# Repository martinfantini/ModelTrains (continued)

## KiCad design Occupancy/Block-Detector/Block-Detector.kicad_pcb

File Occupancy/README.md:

# ModelTrains

This repository contains all the necesarry information to develop an model trains mock-up

## DCC Central

Here is all the information related to the DCC central, which has a DCC booster, to have more than 2A of the output current.

## Expander

Here is the expander connected to the central, to have more input/output configuation.

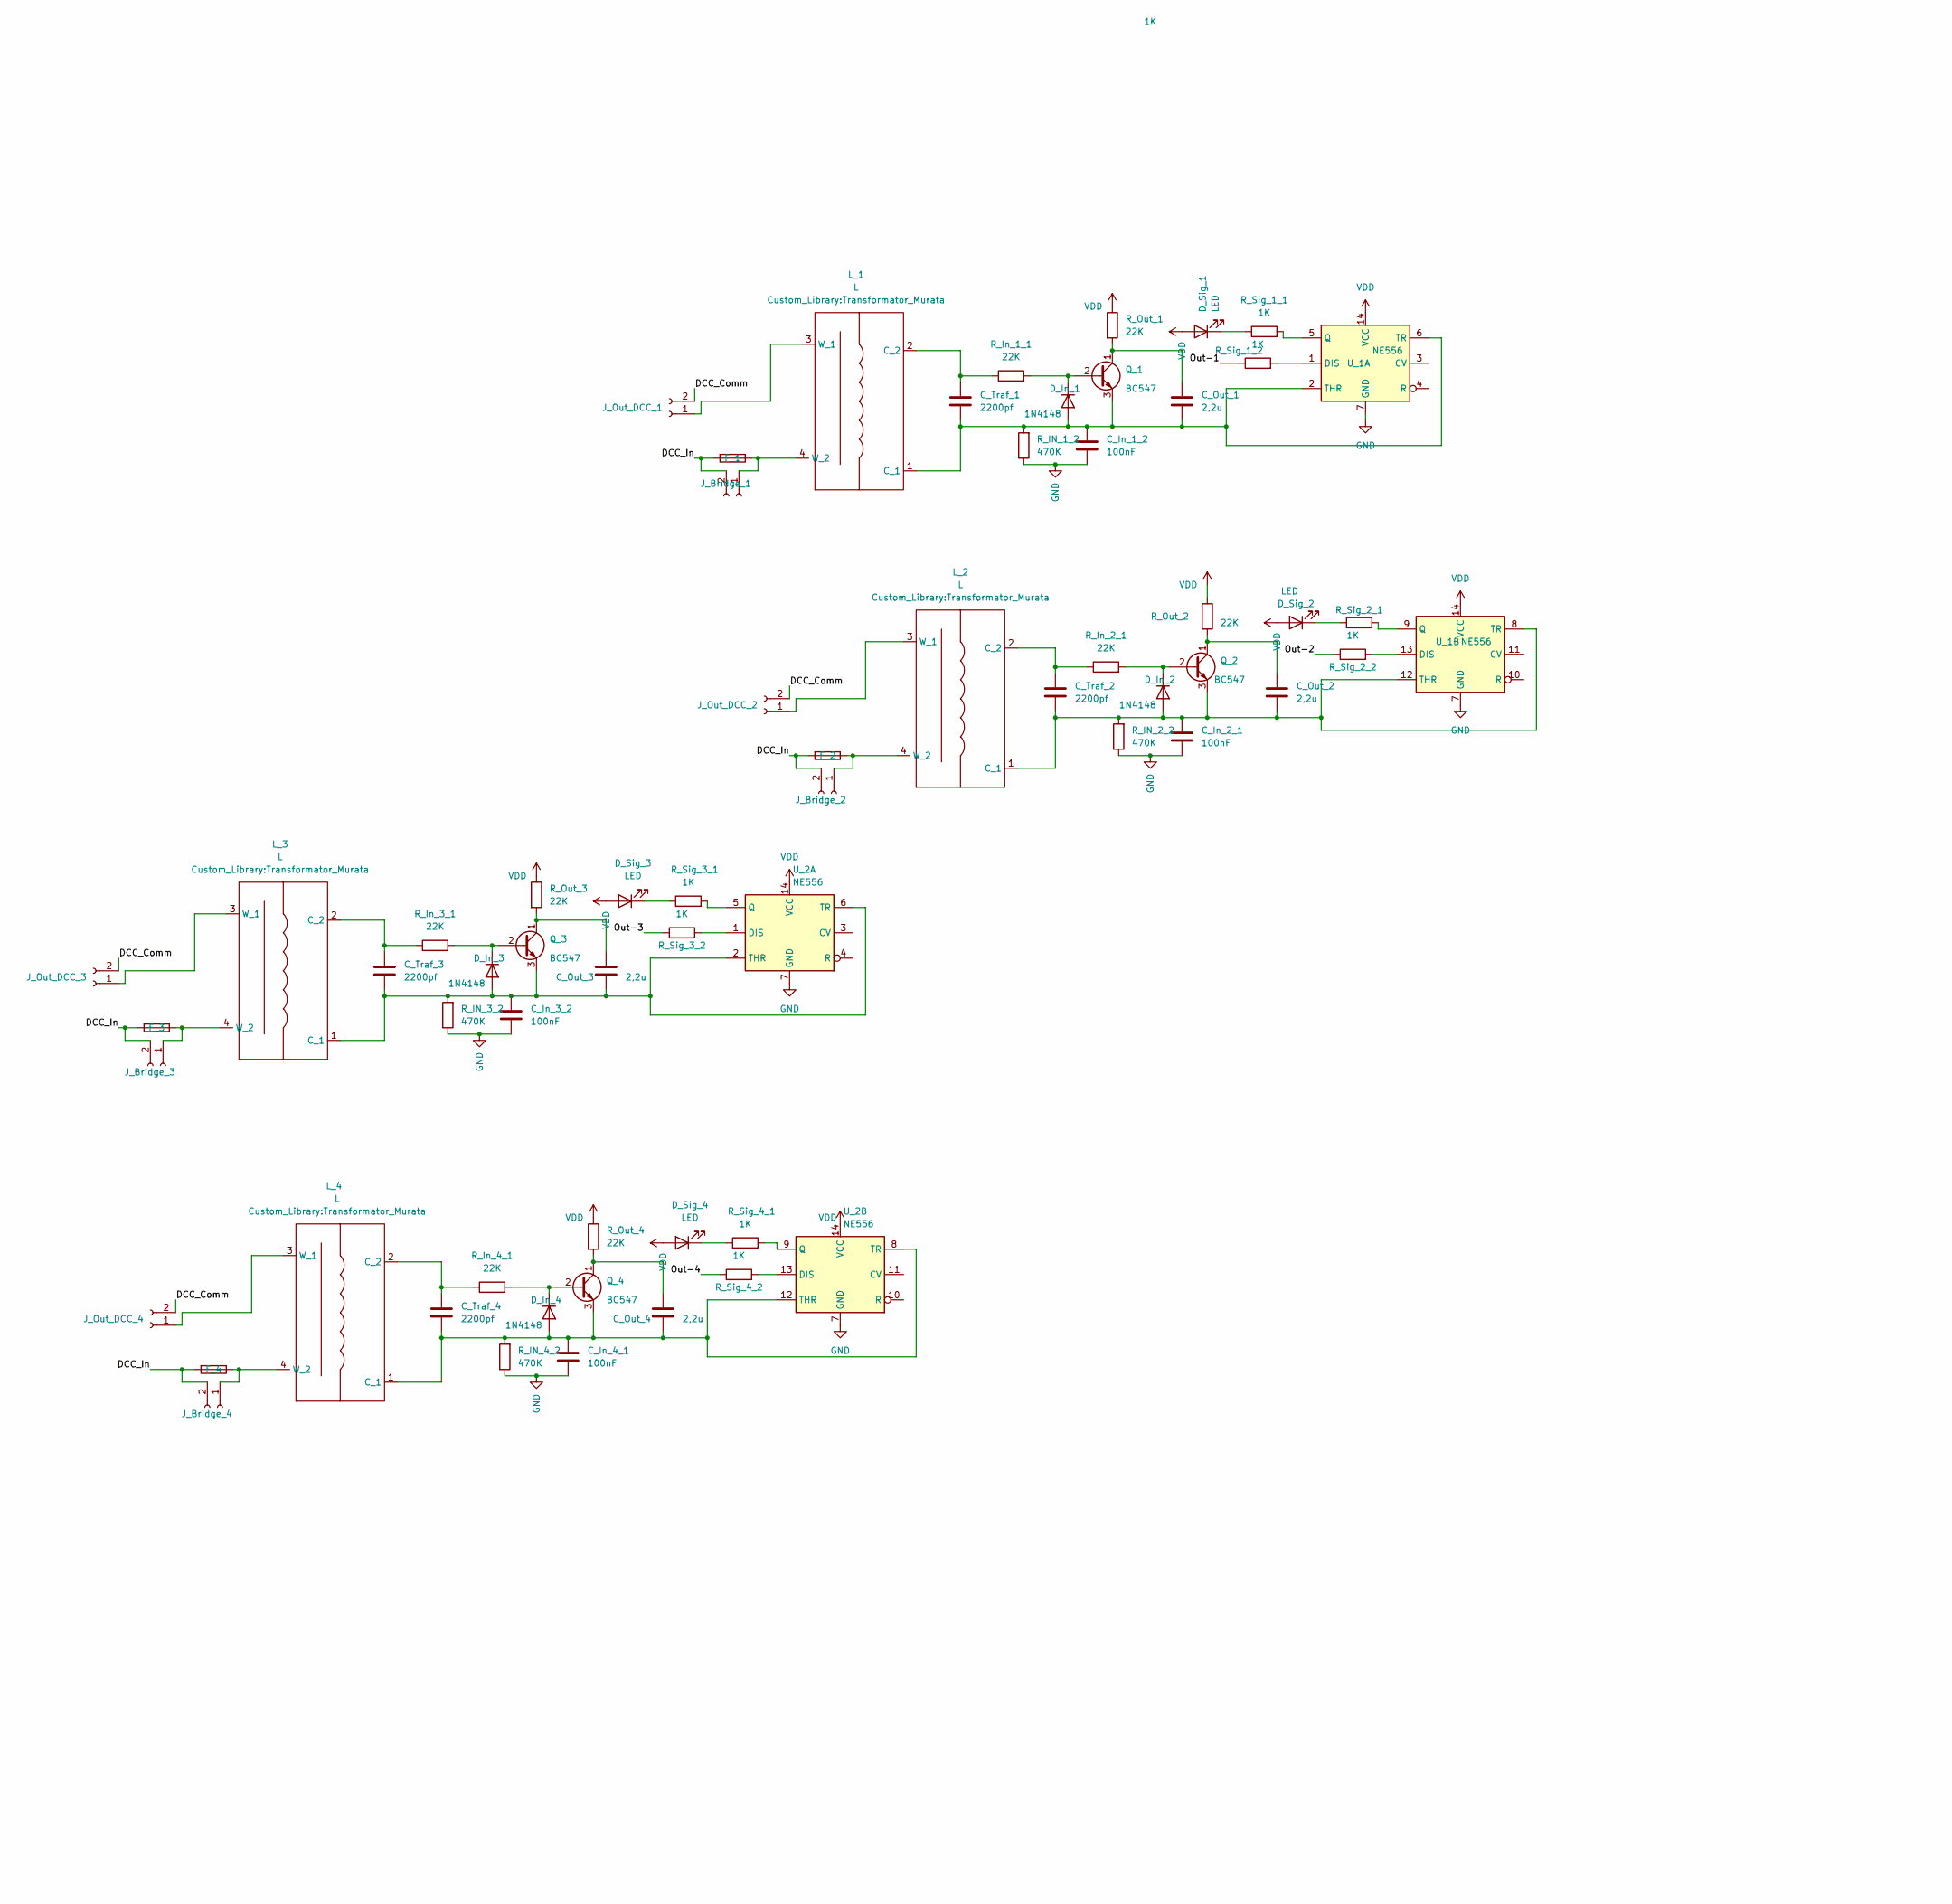
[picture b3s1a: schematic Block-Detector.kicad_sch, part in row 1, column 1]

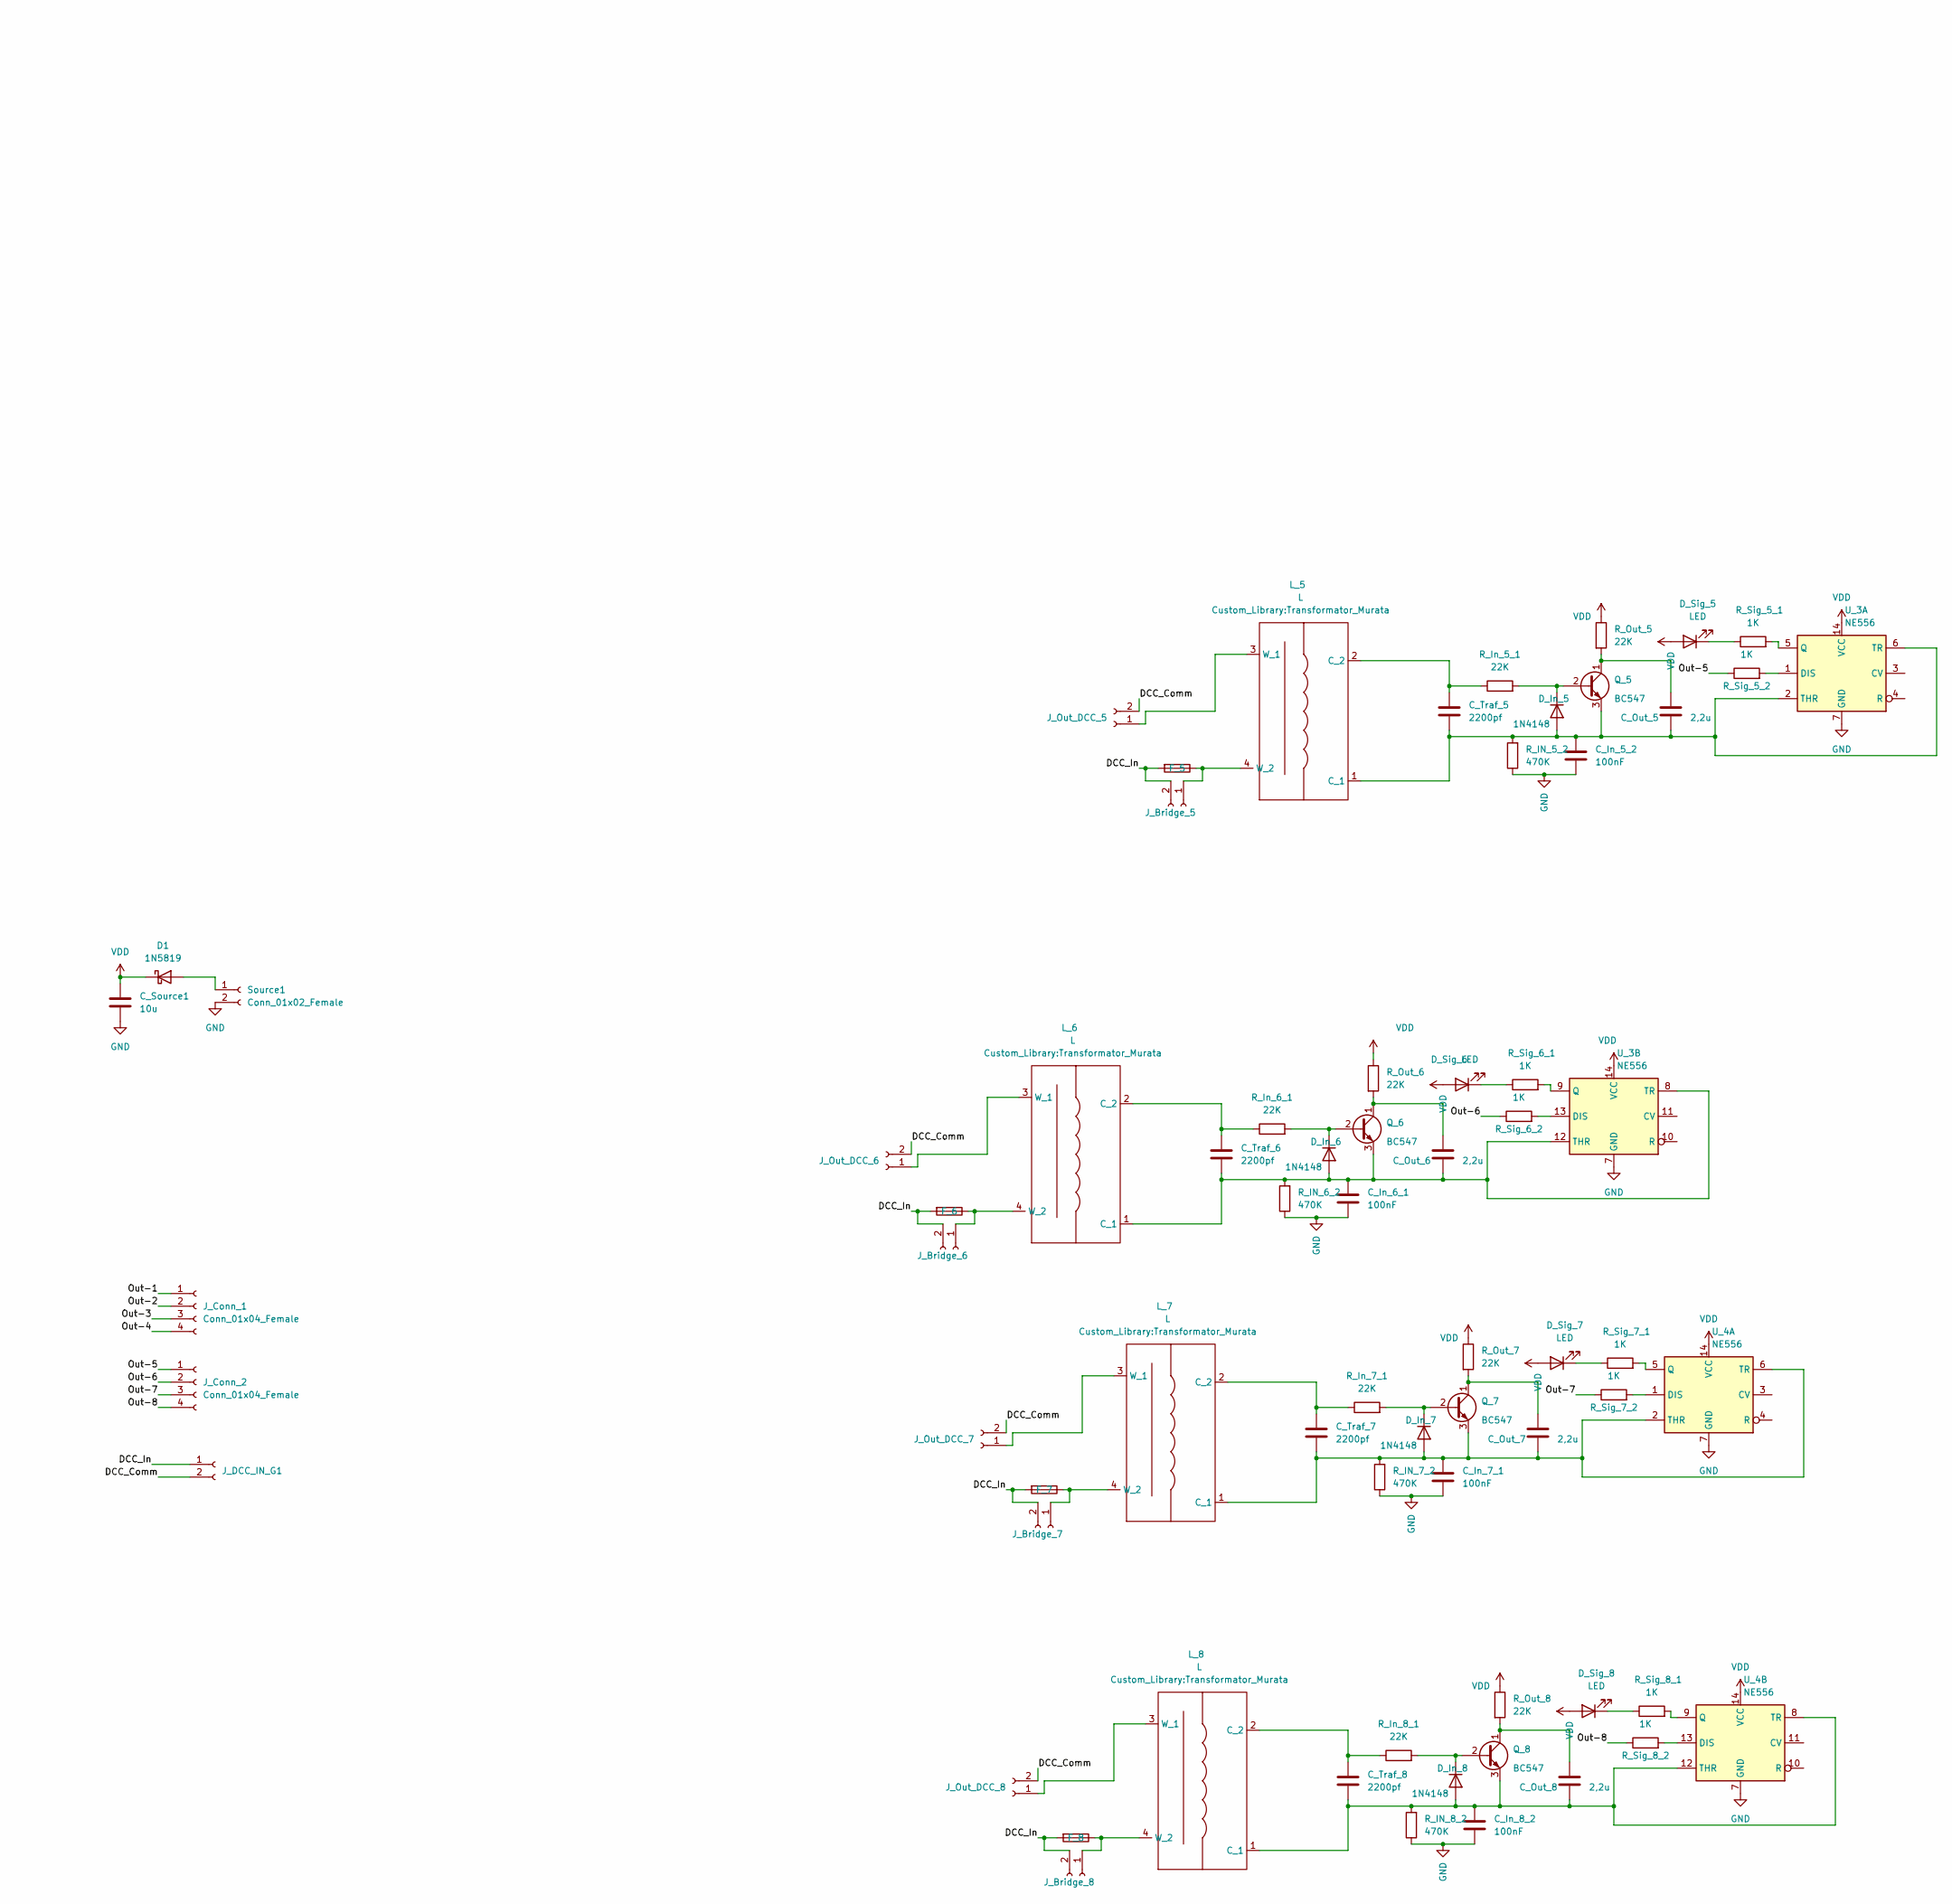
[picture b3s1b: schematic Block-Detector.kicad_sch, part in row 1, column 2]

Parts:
C_In_1_2, C_In_2_1, C_In_3_2, C_In_4_1, C_In_5_2, C_In_6_1, C_In_7_1, C_In_8_2: 100nF; C_Disc_D3.8mm_W2.6mm_P2.50mm
C_Out_1, C_Out_2, C_Out_3, C_Out_4, C_Out_5, C_Out_6, C_Out_7, C_Out_8: 2,2u; C_Disc_D3.8mm_W2.6mm_P2.50mm
C_Source1: 10u; C_Axial_L3.8mm_D2.6mm_P7.50mm_Horizontal
C_Traf_1, C_Traf_2, C_Traf_3, C_Traf_4, C_Traf_5, C_Traf_6, C_Traf_7, C_Traf_8: 2200pf; C_Rect_L7.0mm_W2.5mm_P5.00mm
D1: 1N5819; D_DO-41_SOD81_P10.16mm_Horizontal
D_In_1, D_In_2, D_In_3, D_In_4, D_In_5, D_In_6, D_In_7, D_In_8: 1N4148; D_DO-35_SOD27_P7.62mm_Horizontal
D_Sig_1, D_Sig_2, D_Sig_3, D_Sig_4, D_Sig_5, D_Sig_6, D_Sig_7, D_Sig_8: LED; LED_D5.0mm
F_1, F_2, F_3, F_4, F_5, F_6, F_7, F_8: 1A; Fuseholder_Clip-5x20mm_Keystone_3512_Inline_P23.62x7.27mm_D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
J_Bridge_1, J_Bridge_2, J_Bridge_3, J_Bridge_4, J_Bridge_5, J_Bridge_6, J_Bridge_7, J_Bridge_8: Conn_01x02_Female; LED_2512_6332Metric
J_Conn_1, J_Conn_2: Conn_01x04_Female; Wago_734-134_1x04_P3.50mm_Vertical
J_DCC_IN_G1: Conn_01x02_Female; Wago_734-132_1x02_P3.50mm_Vertical
J_Out_DCC_1, J_Out_DCC_2, J_Out_DCC_3, J_Out_DCC_4, J_Out_DCC_5, J_Out_DCC_6, J_Out_DCC_7, J_Out_DCC_8: Conn_01x02_Female; Wago_734-132_1x02_P3.50mm_Vertical
L_1, L_2, L_3, L_4, L_5, L_6, L_7, L_8: L; Transformator_Murata
Q_1, Q_2, Q_3, Q_4, Q_5, Q_6, Q_7, Q_8: BC547; TO-92_Inline
R_IN_1_2, R_IN_2_2, R_IN_3_2, R_IN_4_2, R_IN_5_2, R_IN_6_2, R_IN_7_2, R_IN_8_2: 470K; R_Axial_DIN0309_L9.0mm_D3.2mm_P12.70mm_Horizontal
R_In_1_1, R_In_2_1, R_In_3_1, R_In_4_1, R_In_5_1, R_In_6_1, R_In_7_1, R_In_8_1: 22K; R_Axial_DIN0309_L9.0mm_D3.2mm_P12.70mm_Horizontal
R_Out_1, R_Out_2, R_Out_3, R_Out_4, R_Out_5, R_Out_6, R_Out_7, R_Out_8: 22K; R_Axial_DIN0309_L9.0mm_D3.2mm_P12.70mm_Horizontal
R_Sig_1_1, R_Sig_1_2, R_Sig_2_1, R_Sig_2_2, R_Sig_3_1, R_Sig_3_2, R_Sig_4_1, R_Sig_4_2, R_Sig_5_1, R_Sig_5_2, R_Sig_6_1, R_Sig_6_2, R_Sig_7_1, R_Sig_7_2, R_Sig_8_1, R_Sig_8_2: 1K; R_Axial_DIN0309_L9.0mm_D3.2mm_P12.70mm_Horizontal
Source1: Conn_01x02_Female; JST_NV_B02P-NV_1x02_P5.00mm_Vertical
U_1, U_2, U_3, U_4: NE556; DIP-14_W7.62mm_Socket_LongPads

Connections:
/DCC_Comm: J_DCC_IN_G1.2, J_Out_DCC_1.2, J_Out_DCC_2.2, J_Out_DCC_3.2, J_Out_DCC_4.2, J_Out_DCC_5.2, J_Out_DCC_6.2, J_Out_DCC_7.2, J_Out_DCC_8.2
/DCC_In: F_1.2, F_2.2, F_3.2, F_4.2, F_5.2, F_6.2, F_7.2, F_8.2, J_Bridge_1.2, J_Bridge_2.2, J_Bridge_3.2, J_Bridge_4.2, J_Bridge_5.2, J_Bridge_6.2, J_Bridge_7.2, J_Bridge_8.2, J_DCC_IN_G1.1
/Out-1: J_Conn_1.1, R_Sig_1_2.1
/Out-2: J_Conn_1.2, R_Sig_2_2.1
/Out-3: J_Conn_1.3, R_Sig_3_2.1
/Out-4: J_Conn_1.4, R_Sig_4_2.1
/Out-5: J_Conn_2.1, R_Sig_5_2.1
/Out-6: J_Conn_2.2, R_Sig_6_2.1
/Out-7: J_Conn_2.3, R_Sig_7_2.1
/Out-8: J_Conn_2.4, R_Sig_8_2.1
GND: C_In_1_2.2, C_In_2_1.2, C_In_3_2.2, C_In_4_1.2, C_In_5_2.2, C_In_6_1.2, C_In_7_1.2, C_In_8_2.2, C_Source1.2, R_IN_1_2.1, R_IN_2_2.1, R_IN_3_2.1, R_IN_4_2.1, R_IN_5_2.1, R_IN_6_2.1, R_IN_7_2.1, R_IN_8_2.1, Source1.2, U_1.7 (GND), U_2.7 (GND), U_3.7 (GND), U_4.7 (GND)
unnamed: C_In_1_2.1, C_Out_1.2, C_Traf_1.2, D_In_1.2 (A), L_1.1 (C_1), Q_1.3 (E), R_IN_1_2.2, U_1.2 (THR), U_1.6 (TR)
unnamed: C_In_2_1.1, C_Out_2.2, C_Traf_2.2, D_In_2.2 (A), L_2.1 (C_1), Q_2.3 (E), R_IN_2_2.2, U_1.8 (TR), U_1.12 (THR)
unnamed: C_In_3_2.1, C_Out_3.2, C_Traf_3.2, D_In_3.2 (A), L_3.1 (C_1), Q_3.3 (E), R_IN_3_2.2, U_2.2 (THR), U_2.6 (TR)
unnamed: C_In_4_1.1, C_Out_4.2, C_Traf_4.2, D_In_4.2 (A), L_4.1 (C_1), Q_4.3 (E), R_IN_4_2.2, U_2.8 (TR), U_2.12 (THR)
unnamed: C_In_5_2.1, C_Out_5.2, C_Traf_5.2, D_In_5.2 (A), L_5.1 (C_1), Q_5.3 (E), R_IN_5_2.2, U_3.2 (THR), U_3.6 (TR)
unnamed: C_In_6_1.1, C_Out_6.2, C_Traf_6.2, D_In_6.2 (A), L_6.1 (C_1), Q_6.3 (E), R_IN_6_2.2, U_3.8 (TR), U_3.12 (THR)
unnamed: C_In_7_1.1, C_Out_7.2, C_Traf_7.2, D_In_7.2 (A), L_7.1 (C_1), Q_7.3 (E), R_IN_7_2.2, U_4.2 (THR), U_4.6 (TR)
unnamed: C_In_8_2.1, C_Out_8.2, C_Traf_8.2, D_In_8.2 (A), L_8.1 (C_1), Q_8.3 (E), R_IN_8_2.2, U_4.8 (TR), U_4.12 (THR)
unnamed: C_Out_1.1, Q_1.1 (C), R_Out_1.2
unnamed: C_Out_2.1, Q_2.1 (C), R_Out_2.2
unnamed: C_Out_3.1, Q_3.1 (C), R_Out_3.2
unnamed: C_Out_4.1, Q_4.1 (C), R_Out_4.2
unnamed: C_Out_5.1, Q_5.1 (C), R_Out_5.2
unnamed: C_Out_6.1, Q_6.1 (C), R_Out_6.2
unnamed: C_Out_7.1, Q_7.1 (C), R_Out_7.2
unnamed: C_Out_8.1, Q_8.1 (C), R_Out_8.2
unnamed: C_Traf_1.1, L_1.2 (C_2), R_In_1_1.1
unnamed: C_Traf_2.1, L_2.2 (C_2), R_In_2_1.1
unnamed: C_Traf_3.1, L_3.2 (C_2), R_In_3_1.1
unnamed: C_Traf_4.1, L_4.2 (C_2), R_In_4_1.1
unnamed: C_Traf_5.1, L_5.2 (C_2), R_In_5_1.1
unnamed: C_Traf_6.1, L_6.2 (C_2), R_In_6_1.1
unnamed: C_Traf_7.1, L_7.2 (C_2), R_In_7_1.1
unnamed: C_Traf_8.1, L_8.2 (C_2), R_In_8_1.1
unnamed: D1.2 (A), Source1.1
unnamed: D_In_1.1 (K), Q_1.2 (B), R_In_1_1.2
unnamed: D_In_2.1 (K), Q_2.2 (B), R_In_2_1.2
unnamed: D_In_3.1 (K), Q_3.2 (B), R_In_3_1.2
unnamed: D_In_4.1 (K), Q_4.2 (B), R_In_4_1.2
unnamed: D_In_5.1 (K), Q_5.2 (B), R_In_5_1.2
unnamed: D_In_6.1 (K), Q_6.2 (B), R_In_6_1.2
unnamed: D_In_7.1 (K), Q_7.2 (B), R_In_7_1.2
unnamed: D_In_8.1 (K), Q_8.2 (B), R_In_8_1.2
unnamed: D_Sig_1.1 (K), R_Sig_1_1.1
unnamed: D_Sig_2.1 (K), R_Sig_2_1.1
unnamed: D_Sig_3.1 (K), R_Sig_3_1.1
unnamed: D_Sig_4.1 (K), R_Sig_4_1.1
unnamed: D_Sig_5.1 (K), R_Sig_5_1.1
unnamed: D_Sig_6.1 (K), R_Sig_6_1.1
unnamed: D_Sig_7.1 (K), R_Sig_7_1.1
unnamed: D_Sig_8.1 (K), R_Sig_8_1.1
unnamed: F_1.1, J_Bridge_1.1, L_1.4 (W_2)
unnamed: F_2.1, J_Bridge_2.1, L_2.4 (W_2)
unnamed: F_3.1, J_Bridge_3.1, L_3.4 (W_2)
unnamed: F_4.1, J_Bridge_4.1, L_4.4 (W_2)
unnamed: F_5.1, J_Bridge_5.1, L_5.4 (W_2)
unnamed: F_6.1, J_Bridge_6.1, L_6.4 (W_2)
unnamed: F_7.1, J_Bridge_7.1, L_7.4 (W_2)
unnamed: F_8.1, J_Bridge_8.1, L_8.4 (W_2)
unnamed: J_Out_DCC_1.1, L_1.3 (W_1)
unnamed: J_Out_DCC_2.1, L_2.3 (W_1)
unnamed: J_Out_DCC_3.1, L_3.3 (W_1)
unnamed: J_Out_DCC_4.1, L_4.3 (W_1)
unnamed: J_Out_DCC_5.1, L_5.3 (W_1)
unnamed: J_Out_DCC_6.1, L_6.3 (W_1)
unnamed: J_Out_DCC_7.1, L_7.3 (W_1)
unnamed: J_Out_DCC_8.1, L_8.3 (W_1)
unnamed: R_Sig_1_1.2, U_1.5 (Q)
unnamed: R_Sig_1_2.2, U_1.1 (DIS)
unnamed: R_Sig_2_1.2, U_1.9 (Q)
unnamed: R_Sig_2_2.2, U_1.13 (DIS)
unnamed: R_Sig_3_1.2, U_2.5 (Q)
unnamed: R_Sig_3_2.2, U_2.1 (DIS)
unnamed: R_Sig_4_1.2, U_2.9 (Q)
unnamed: R_Sig_4_2.2, U_2.13 (DIS)
unnamed: R_Sig_5_1.2, U_3.5 (Q)
unnamed: R_Sig_5_2.2, U_3.1 (DIS)
unnamed: R_Sig_6_1.2, U_3.9 (Q)
unnamed: R_Sig_6_2.2, U_3.13 (DIS)
unnamed: R_Sig_7_1.2, U_4.5 (Q)
unnamed: R_Sig_7_2.2, U_4.1 (DIS)
unnamed: R_Sig_8_1.2, U_4.9 (Q)
unnamed: R_Sig_8_2.2, U_4.13 (DIS)
VDD: C_Source1.1, D1.1 (K), D_Sig_1.2 (A), D_Sig_2.2 (A), D_Sig_3.2 (A), D_Sig_4.2 (A), D_Sig_5.2 (A), D_Sig_6.2 (A), D_Sig_7.2 (A), D_Sig_8.2 (A), R_Out_1.1, R_Out_2.1, R_Out_3.1, R_Out_4.1, R_Out_5.1, R_Out_6.1, R_Out_7.1, R_Out_8.1, U_1.14 (VCC), U_2.14 (VCC), U_3.14 (VCC), U_4.14 (VCC)

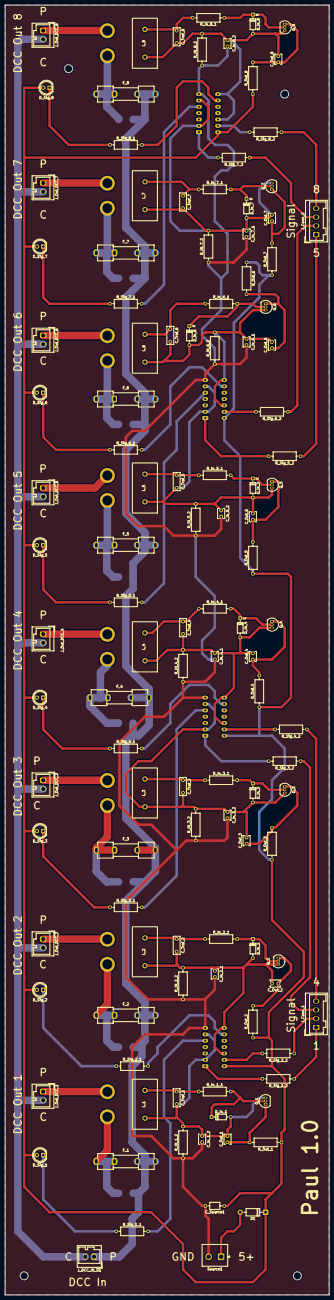
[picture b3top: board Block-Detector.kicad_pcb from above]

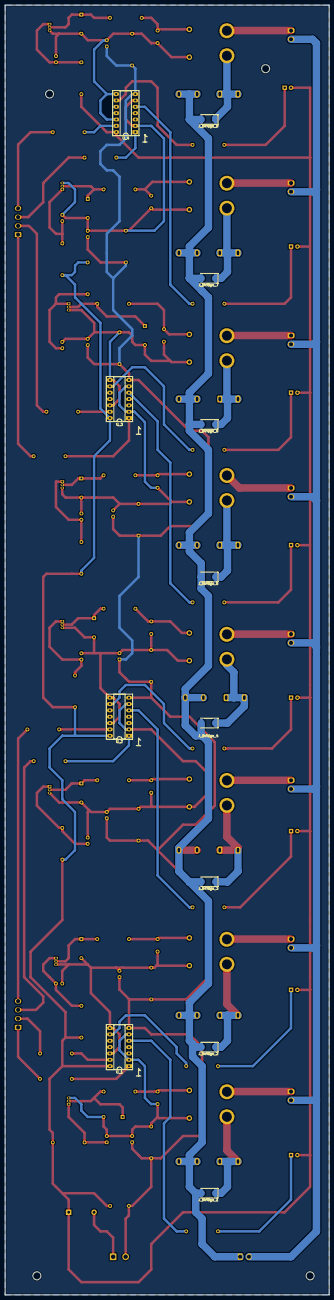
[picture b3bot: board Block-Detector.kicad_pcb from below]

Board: 2 copper layers, 129.5 x 515.6 mm, 130 parts (12 on the bottom side), 85 nets.

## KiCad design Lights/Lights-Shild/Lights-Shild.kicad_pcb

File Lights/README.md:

# Lights

For this modele, I use the [SBC-USR-ES1 module](./SBC-USR-ES1_MANUAL_2021-04-22.pdf) and the Arduino AT Mega 328.

## Lights-Shild

Here is the circuit board of this project.

## ArtnetReceiver

Here is the code of the Lights-Shild, using the [SBC-USR-ES1 module](./SBC-USR-ES1_MANUAL_2021-04-22.pdf) module.
The IP definied for this module is start and you have to change in code:

```c
//DEFINE THE IP HERE WICH HEARS ARNET MESSAGES
byte ip[] = {192, 16, 178, 205};
```

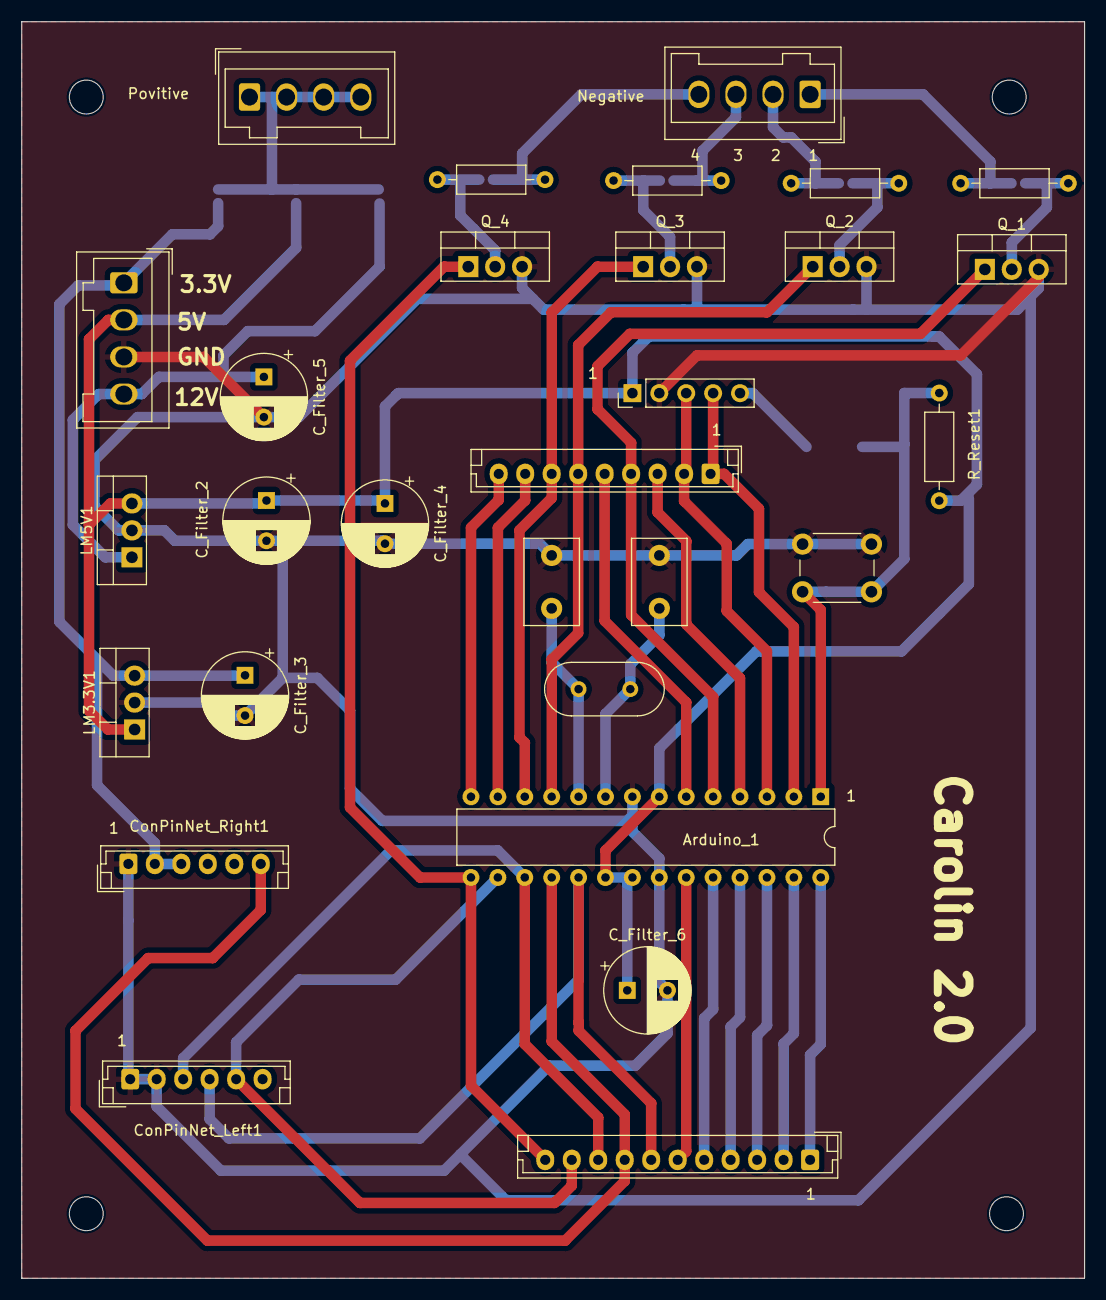
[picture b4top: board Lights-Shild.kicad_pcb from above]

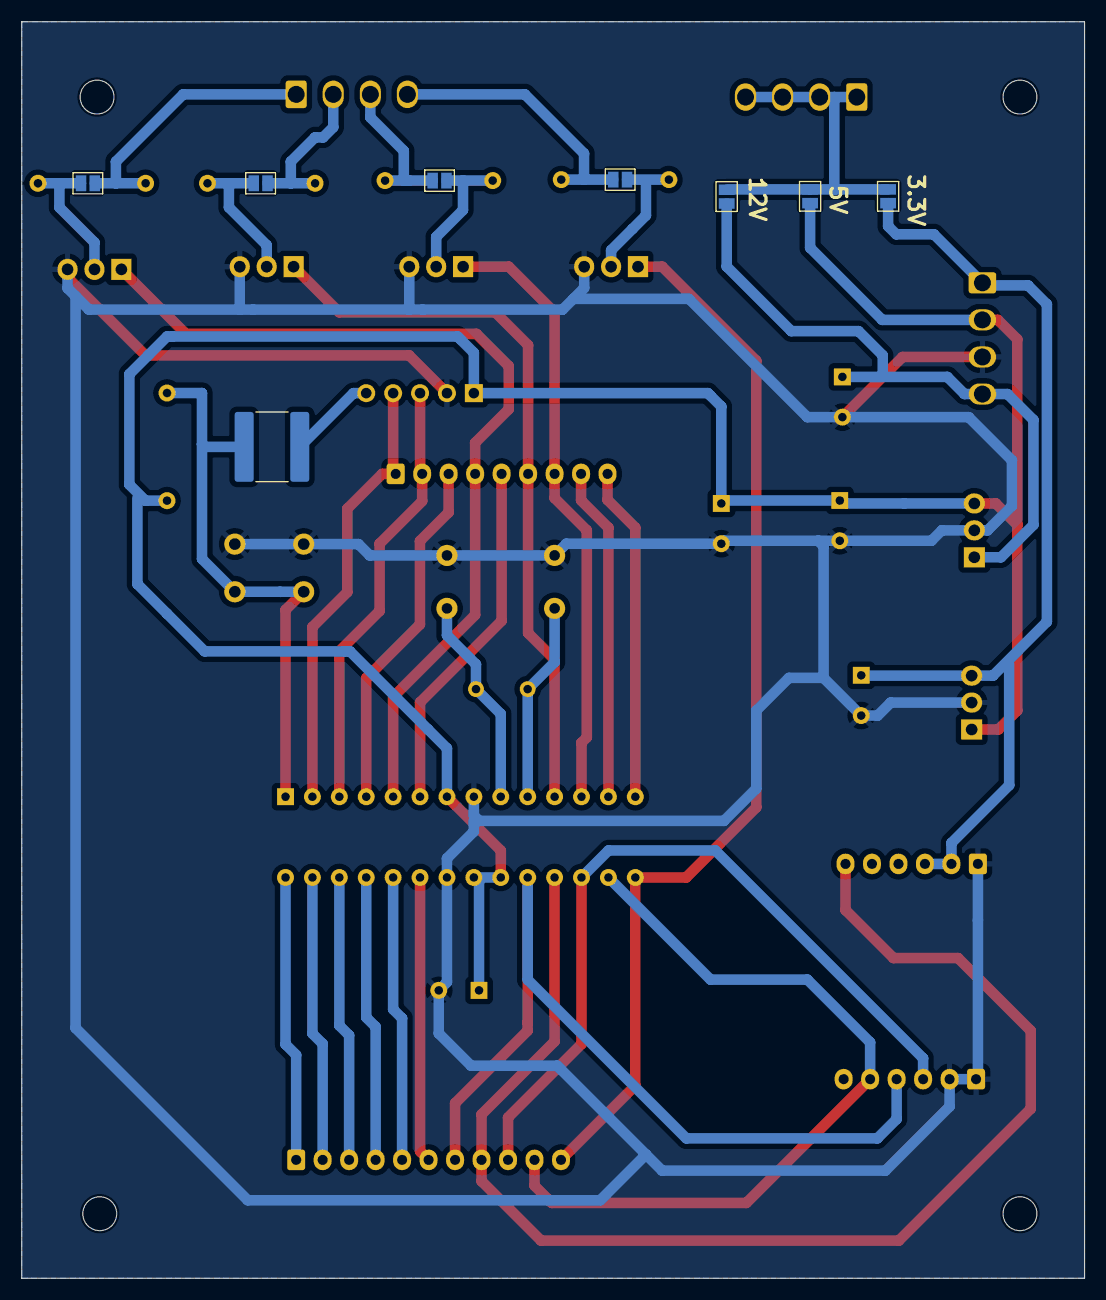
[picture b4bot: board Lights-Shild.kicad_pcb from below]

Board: 2 copper layers, 100.3 x 118.6 mm, 37 parts (8 on the bottom side), 37 nets.

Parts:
Arduino_1: ATmega328-P; DIP-28_W7.62mm
C_Filter_2, C_Filter_3, C_Filter_4, C_Filter_5, C_Filter_6: 47uF; CP_Radial_D8.0mm_P3.80mm
C_Rest1: 100nF; C_2225_5664Metric_Pad1.80x6.60mm_HandSolder
C_XTAL_1, C_XTAL_2: 22 pF; C_Disc_D8.0mm_W5.0mm_P5.00mm
ConPinNet_Left1: Conn_01x06_Pin; JST_EH_B6B-EH-A_1x06_P2.50mm_Vertical
ConPinNet_Right1: Conn_01x06_Pin; JST_EH_B6B-EH-A_1x06_P2.50mm_Vertical
Con_In1: Conn_01x04; Wago_734-134_1x04_P3.50mm_Vertical
Con_Light_Neg1: Conn_01x04; Wago_734-134_1x04_P3.50mm_Vertical
Con_Light_Pos1: Conn_01x04; Wago_734-134_1x04_P3.50mm_Vertical
Conn_Debuger_1: Debuger; PinHeader_1x05_P2.54mm_Vertical
J1: Conn_01x09_Pin; JST_EH_B9B-EH-A_1x09_P2.50mm_Vertical
J2: Conn_01x11_Pin; JST_EH_B11B-EH-A_1x11_P2.50mm_Vertical
JP1: Lig_Jmp_1; SolderJumper-2_P1.3mm_Open_Pad1.0x1.5mm
JP2: Lig_Jmp_2; SolderJumper-2_P1.3mm_Open_Pad1.0x1.5mm
JP3: Lig_Jmp_3; SolderJumper-2_P1.3mm_Open_Pad1.0x1.5mm
JP4: Lig_Jmp_4; SolderJumper-2_P1.3mm_Open_Pad1.0x1.5mm
JP_3.3V1: 3.3V_Pos; SolderJumper-2_P1.3mm_Open_Pad1.0x1.5mm
JP_5V1: 5V_Pos; SolderJumper-2_P1.3mm_Open_Pad1.0x1.5mm
JP_12V1: 12V_Pos; SolderJumper-2_P1.3mm_Open_Pad1.0x1.5mm
LM3.3V1, LM5V1: LM2937xT; TO-220-3_Vertical
Q_1, Q_2, Q_3, Q_4: IRLB8721PBF; TO-220-3_Vertical
R1: R1; R_Axial_DIN0207_L6.3mm_D2.5mm_P10.16mm_Horizontal
R2: R2; R_Axial_DIN0207_L6.3mm_D2.5mm_P10.16mm_Horizontal
R3: R3; R_Axial_DIN0207_L6.3mm_D2.5mm_P10.16mm_Horizontal
R4: R4; R_Axial_DIN0207_L6.3mm_D2.5mm_P10.16mm_Horizontal
R_Reset1: 10K; R_Axial_DIN0207_L6.3mm_D2.5mm_P10.16mm_Horizontal
SW_reset1: SW_DIP_x01; SW_PUSH_6mm_H5mm
XTAL1: Crystal 16 Mhz; Crystal_HC49-U_Vertical

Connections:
+3.3V: C_Filter_3.1, ConPinNet_Right1.2, ConPinNet_Right1.3, Con_In1.1, JP_3.3V1.1 (A), LM3.3V1.3 (VO)
+5V: Arduino_1.7 (VCC), Arduino_1.20 (AVCC), Arduino_1.21 (AREF), C_Filter_2.1, C_Filter_4.1, C_Filter_6.1, Con_In1.2, Conn_Debuger_1.1, JP_5V1.1 (A), LM3.3V1.1 (VI), LM5V1.3 (VO), R_Reset1.1
+12V: C_Filter_5.1, Con_In1.4, JP_12V1.1 (A), LM5V1.1 (VI)
Earth: Arduino_1.8 (GND), Arduino_1.22 (GND), C_Filter_2.2, C_Filter_3.2, C_Filter_4.2, C_Filter_5.2, C_Filter_6.2, C_XTAL_1.2, C_XTAL_2.2, ConPinNet_Left1.1, ConPinNet_Left1.2, ConPinNet_Right1.1, Con_In1.3, Conn_Debuger_1.2, LM3.3V1.2 (GND), LM5V1.2 (GND), Q_1.3 (S), Q_2.3 (S), Q_3.3 (S), Q_4.3 (S), SW_reset1.1
unnamed: Arduino_1.14 (PB0), J1.9
unnamed: Arduino_1.15 (PB1), J2.11, Q_4.1 (G)
unnamed: Arduino_1.16 (PB2), ConPinNet_Left1.5, J2.10
unnamed: Arduino_1.17 (PB3), ConPinNet_Left1.3, J2.9
unnamed: Arduino_1.18 (PB4), ConPinNet_Right1.6, J2.8
unnamed: Arduino_1.19 (PB5), ConPinNet_Left1.4, J2.7
unnamed: Arduino_1.23 (PC0), J2.6
unnamed: Arduino_1.24 (PC1), J2.5
unnamed: Arduino_1.25 (PC2), J2.4
unnamed: Arduino_1.26 (PC3), J2.3
unnamed: Arduino_1.27 (PC4), J2.2
unnamed: Arduino_1.28 (PC5), J2.1
unnamed: Arduino_1.2 (PD0), Conn_Debuger_1.4, J1.1
unnamed: Arduino_1.3 (PD1), Conn_Debuger_1.3, J1.2
unnamed: Arduino_1.4 (PD2), J1.3
unnamed: Arduino_1.5 (PD3), J1.4, Q_1.1 (G)
unnamed: Arduino_1.6 (PD4), J1.5
unnamed: Arduino_1.11 (PD5), J1.6, Q_2.1 (G)
unnamed: Arduino_1.12 (PD6), J1.7, Q_3.1 (G)
unnamed: Arduino_1.13 (PD7), J1.8
unnamed: Arduino_1.9 (XTAL1/PB6), C_XTAL_2.1, XTAL1.2
unnamed: Arduino_1.10 (XTAL2/PB7), C_XTAL_1.1, XTAL1.1
unnamed: Arduino_1.1 (~RESET/PC6), C_Rest1.2, R_Reset1.2, SW_reset1.2
unnamed: Con_Light_Neg1.1, JP1.2 (B), R1.2
unnamed: Con_Light_Neg1.2, JP2.2 (B), R2.2
unnamed: Con_Light_Neg1.3, JP3.2 (B), R3.2
unnamed: Con_Light_Neg1.4, JP4.2 (B), R4.2
unnamed: Con_Light_Pos1.1, Con_Light_Pos1.2, Con_Light_Pos1.3, Con_Light_Pos1.4, JP_3.3V1.2 (B), JP_5V1.2 (B), JP_12V1.2 (B)
unnamed: C_Rest1.1, Conn_Debuger_1.5
unnamed: JP1.1 (A), Q_1.2 (D), R1.1
unnamed: JP2.1 (A), Q_2.2 (D), R2.1
unnamed: JP3.1 (A), Q_3.2 (D), R3.1
unnamed: JP4.1 (A), Q_4.2 (D), R4.1
